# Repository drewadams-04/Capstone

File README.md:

# Capstone
Drew Adams and Michael Jakubisn senior capstone

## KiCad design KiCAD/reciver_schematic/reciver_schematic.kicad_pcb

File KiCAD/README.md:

9/29 - started creating KiCAD schematic

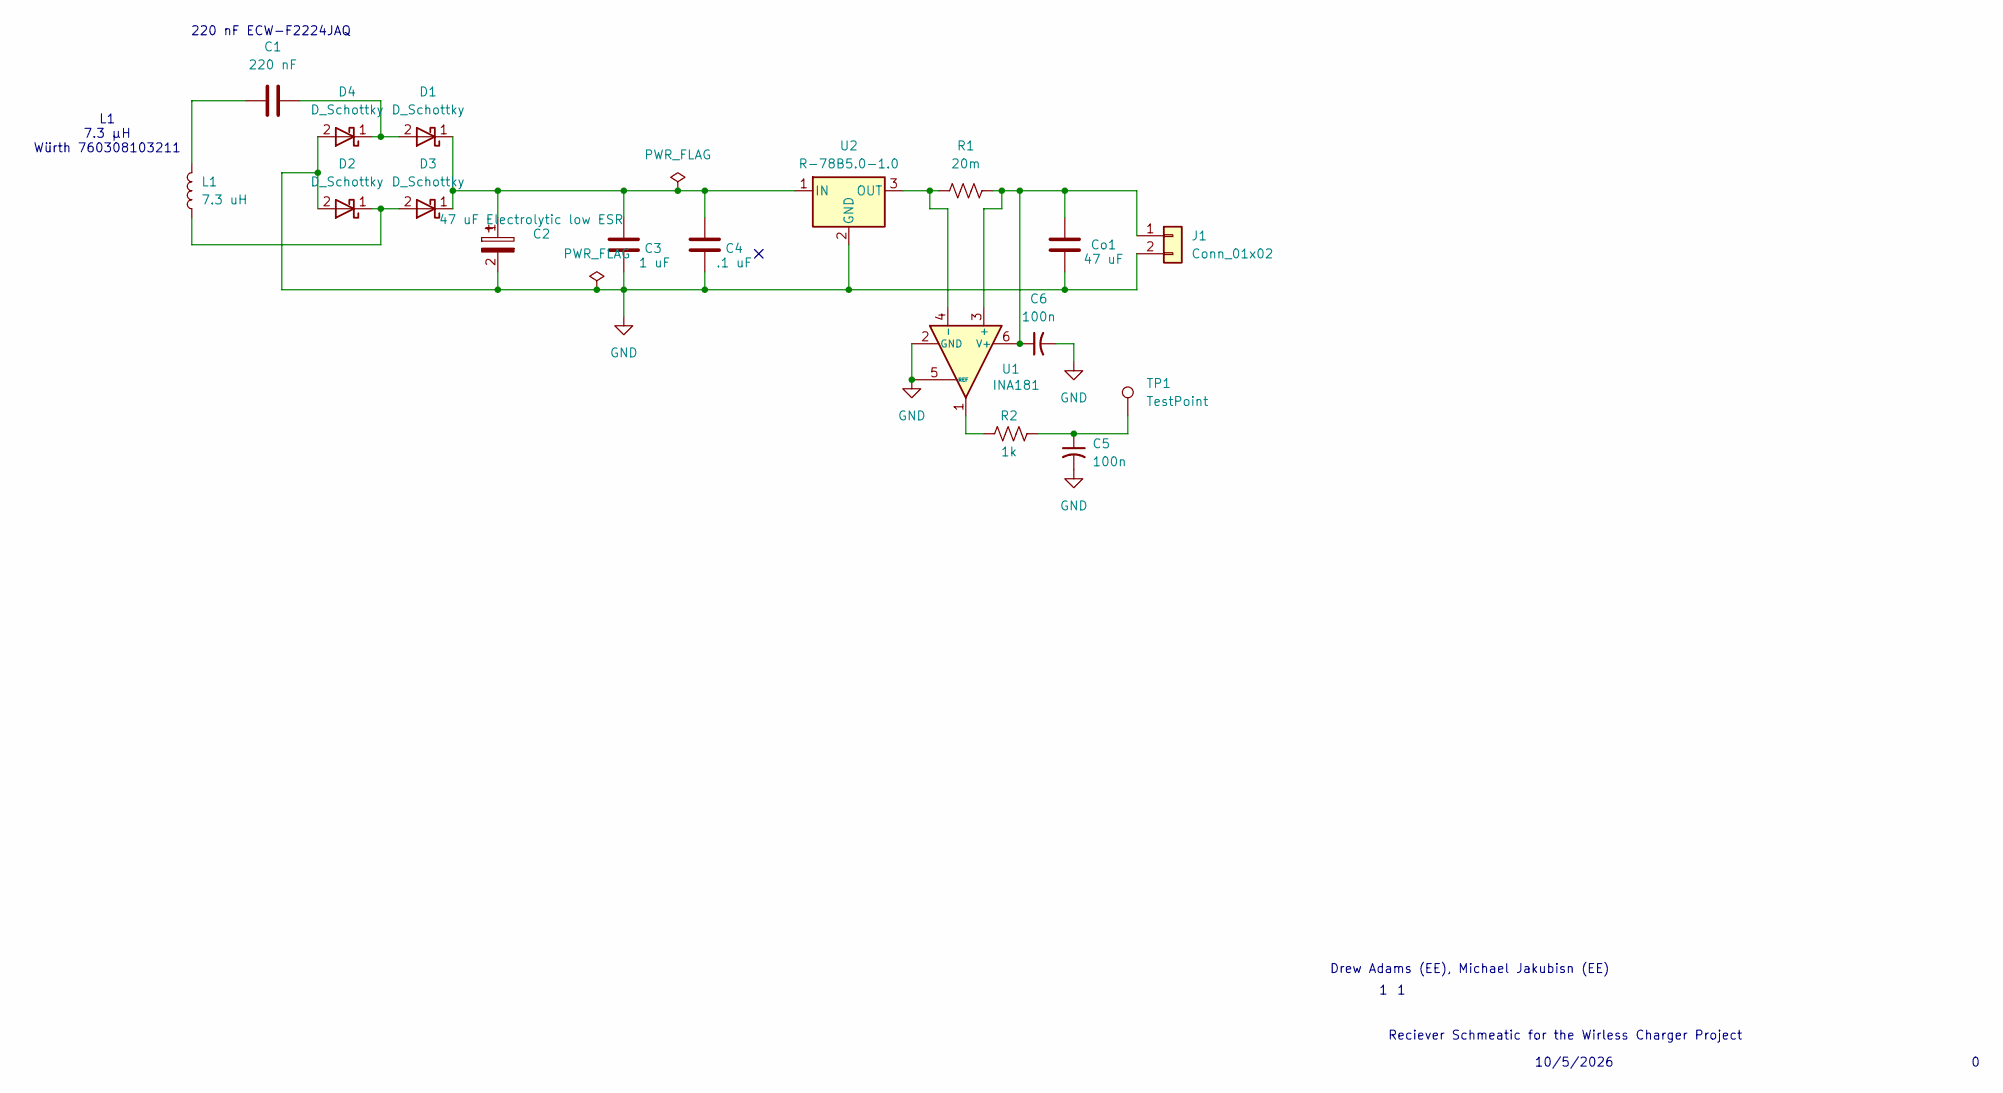
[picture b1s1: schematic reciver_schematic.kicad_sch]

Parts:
C1: 220 nF; C_Rect_L13.0mm_W6.0mm_P10.00mm_FKS3_FKP3_MKS4
C2: 47 uF Electrolytic low ESR; CP_Radial_D6.3mm_P2.50mm
C3: 1 uF; C_Disc_D5.0mm_W2.5mm_P5.00mm
C4: .1 uF; C_Disc_D5.0mm_W2.5mm_P5.00mm
C5, C6: 100n; C_Disc_D5.0mm_W2.5mm_P5.00mm
Co1: 47 uF; CP_Radial_D5.0mm_P2.00mm
D1, D2, D3, D4: D_Schottky; D_DO-15_P10.16mm_Horizontal
J1: Conn_01x02; TerminalBlock_Phoenix_MKDS-1,5-2_1x02_P5.00mm_Horizontal
L1: 7.3 uH; wurth
R1: 20m; R_Axial_DIN0207_L6.3mm_D2.5mm_P7.62mm_Horizontal
R2: 1k; R_Axial_DIN0207_L6.3mm_D2.5mm_P7.62mm_Horizontal
TP1: TestPoint; TestPoint_THTPad_D1.5mm_Drill0.7mm
U1: INA181; SOT-23-6_Handsoldering
U2: R-78B5.0-1.0; CONV_R-78K5.0-1.0

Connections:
GND: C2.2, C3.2, C4.2, C5.2, C6.2, Co1.2, D2.2 (A), D4.2 (A), J1.2, U1.2 (GND), U1.5 (REF), U2.2 (GND)
unnamed: C1.1, L1.2
unnamed: C5.1, R2.2, TP1.1 (1_1)
unnamed: C1.2, D1.2 (A), D4.1 (K)
unnamed: C2.1, C3.1, C4.1, D1.1 (K), D3.1 (K), U2.1 (IN)
unnamed: D2.1 (K), D3.2 (A), L1.1
unnamed: C6.1, Co1.1, J1.1, R1.2, U1.3 (+), U1.6 (V+)
unnamed: R2.1, U1.1
unnamed: R1.1, U1.4 (-), U2.3 (OUT)

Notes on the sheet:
L1 7.3 µH Würth 760308103211
220 nF ECW-F2224JAQ
10/5/2026
Drew Adams (EE), Michael Jakubisn (EE)
Reciever Schmeatic for the Wirless Charger Project

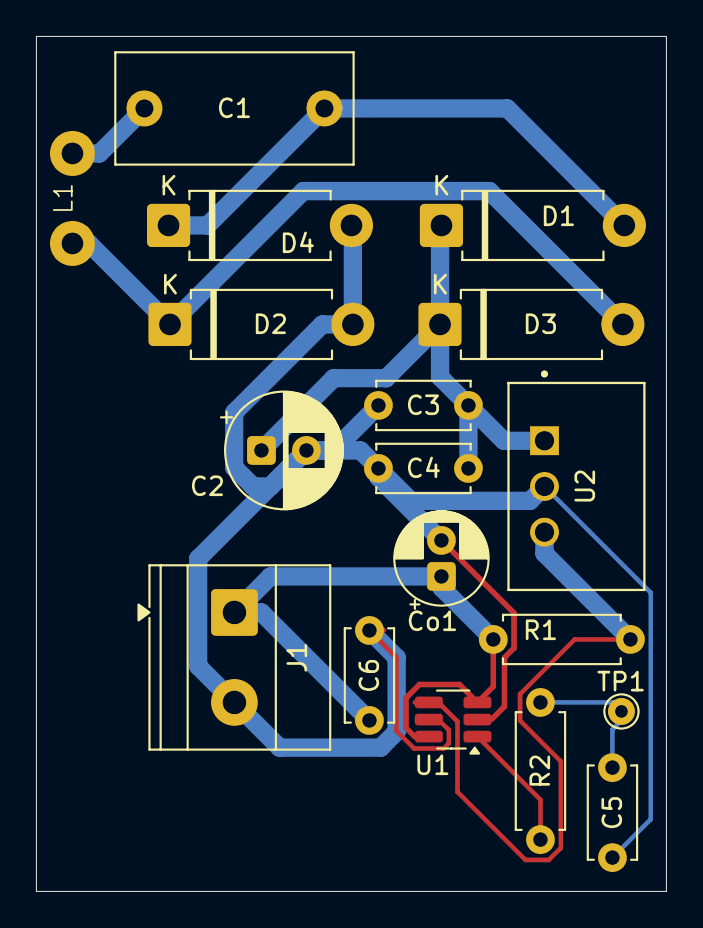
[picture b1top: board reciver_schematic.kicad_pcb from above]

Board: 2 copper layers, 35.0 x 47.5 mm, 18 parts (0 on the bottom side), 9 nets.

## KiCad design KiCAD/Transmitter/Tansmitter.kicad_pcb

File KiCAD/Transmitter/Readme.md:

This is the PCB and Schematic for the transmitter side of the wireless charger

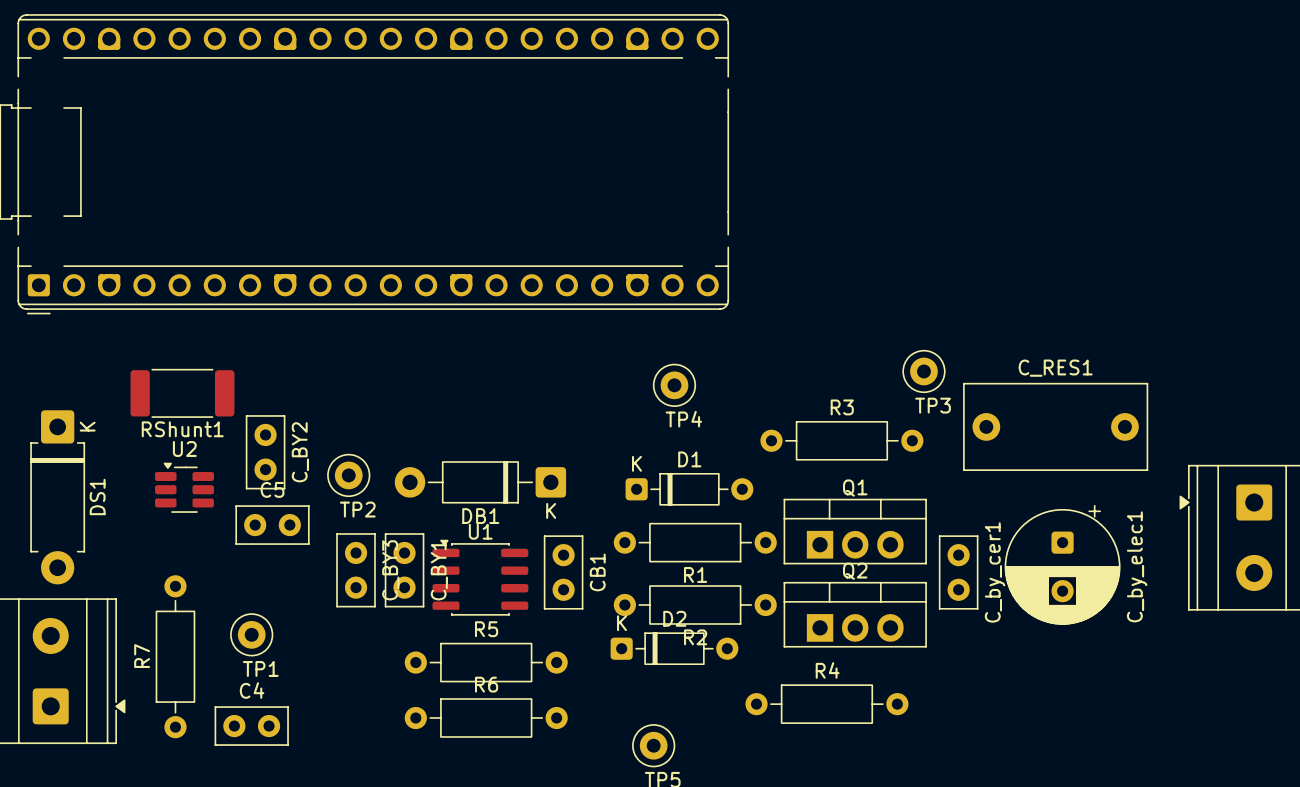
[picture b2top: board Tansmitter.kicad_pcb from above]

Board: 2 copper layers, 33 parts (0 on the bottom side), 16 nets, no tracks yet.

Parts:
A1: RaspberryPi_Pico_W; RaspberryPi_Pico_Common_THT
C4, C5: 100n; C_Disc_D5.0mm_W2.5mm_P2.50mm
CB1: 1u; C_Disc_D5.0mm_W2.5mm_P2.50mm
C_BY1, C_BY2: 100n; C_Disc_D5.0mm_W2.5mm_P2.50mm
C_BY3: 10u; C_Disc_D5.0mm_W2.5mm_P2.50mm
C_RES1: 220n; C_Rect_L13.0mm_W6.0mm_P10.00mm_FKS3_FKP3_MKS4
C_by_cer1: 1u; C_Disc_D5.0mm_W2.5mm_P2.50mm
C_by_elec1: 100u; CP_Radial_D8.0mm_P3.50mm
D1, D2: 1N914; D_DO-35_SOD27_P7.62mm_Horizontal
DB1: 1N5819; D_DO-41_SOD81_P10.16mm_Horizontal
DS1: SB2100; D_DO-15_P10.16mm_Horizontal
J1: 12VDC; TerminalBlock_Phoenix_MKDS-1,5-2-5.08_1x02_P5.08mm_Horizont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
Q1, Q2: IRFB4410Z; TO-220-3_Vertical
R1, R2: 22; R_Axial_DIN0207_L6.3mm_D2.5mm_P10.16mm_Horizontal
R3, R4, R5, R6: 10k; R_Axial_DIN0207_L6.3mm_D2.5mm_P10.16mm_Horizontal
R7: 1k; R_Axial_DIN0207_L6.3mm_D2.5mm_P10.16mm_Horizontal
RShunt1: 0.02; R_2512_6332Metric_Pad1.40x3.35mm_HandSolder
TP1, TP2, TP3, TP4, TP5: TestPoint; TestPoint_Loop_D2.50mm_Drill1.0mm
TX_coil1: 7.3u; TerminalBlock_Phoenix_MKDS-1,5-2-5.08_1x02_P5.08mm_Horizont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
U1: IRS2104; SOIC-8_3.9x4.9mm_P1.27mm
U2: INA181A2; SOT-23-6_Handsoldering

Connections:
+3.3V: A1.36 (3V3), C5.1, U2.6 (V+)
+12V: C_BY1.1, C_BY2.1, C_BY3.1, C_by_cer1.1, C_by_elec1.1, DB1.2 (A), Q1.2 (D), RShunt1.1, TP2.1 (1_1), U1.1 (VCC), U2.4 (-)
GND: A1.3 (GND), A1.8 (GND), A1.13 (GND), A1.18 (GND), A1.23 (GND), A1.28 (GND), A1.38 (GND), C4.2, C5.2, C_BY1.2, C_BY2.2, C_BY3.2, C_by_cer1.2, C_by_elec1.2, J1.1, Q2.3 (S), R4.2, R5.2, R6.2, TX_coil1.2, U1.4 (COM), U2.2 (GND), U2.5 (REF)
unnamed: A1.1 (GPIO0), R6.1, U1.2 (IN)
unnamed: A1.2 (GPIO1), R5.1, U1.3 (~SD)
unnamed: C4.1, R7.1, TP1.1 (1_1)
unnamed: C_RES1.2, TX_coil1.1
unnamed: D1.2 (A), Q1.1 (G), R1.1, R3.1
unnamed: D1.1 (K), R1.2, TP4.1 (1_1), U1.7 (HO)
unnamed: D2.2 (A), Q2.1 (G), R2.1, R4.1
unnamed: D2.1 (K), R2.2, TP5.1 (1_1), U1.5 (LO)
unnamed: CB1.1, DB1.1 (K), U1.8 (VB)
unnamed: DS1.2 (A), J1.2
unnamed: DS1.1 (K), RShunt1.2, U2.3 (+)
unnamed: CB1.2, C_RES1.1, Q1.3 (S), Q2.2 (D), R3.2, TP3.1 (1_1), U1.6 (VS)
unnamed: R7.2, U2.1
